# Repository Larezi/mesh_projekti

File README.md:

# BLE mesh projekti
- Yleiskuvaus  
Projektissa toteutetaan BLE mesh -verkko, joka välittää lämpötila- ja ilmankosteusdataa.  
Verkko muodostuu ESP32-moduuleihin perustuvista solmuista,  
joissa käytetään SHTC3-sensoria lämpötilan ja ilmankosteuden mittaamiseen.  
Solmut välittävät mittausdatan pääsolmulle, jonka kautta data siirretään Raspberry Pi:lle.  
Raspberry Pi toimii gatewayna ja tallentaa datan tietokantaan, josta mittaustietoja voidaan lukea web-käyttöliittymän kautta.  

- Lohkokaavio

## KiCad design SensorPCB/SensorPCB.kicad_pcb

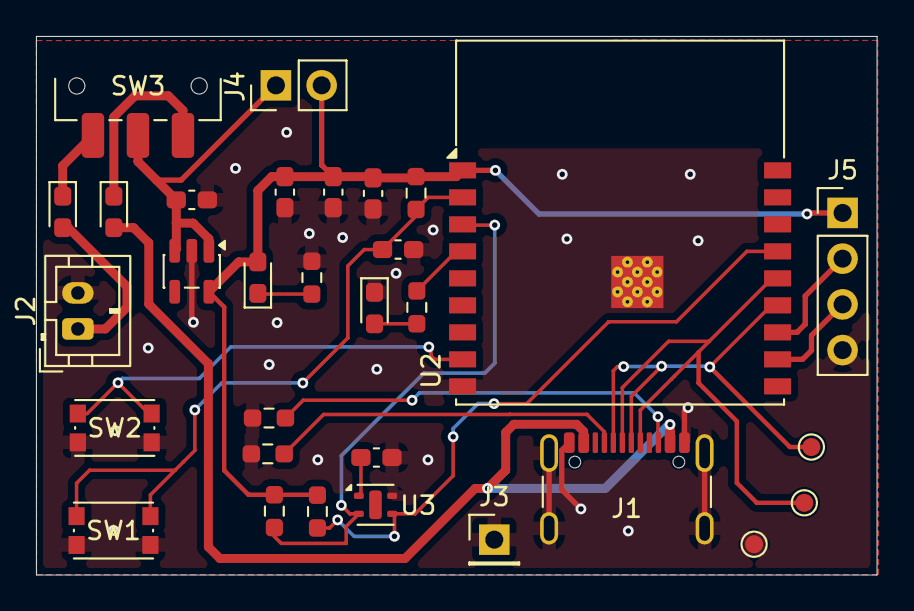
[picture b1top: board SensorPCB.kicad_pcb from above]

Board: 2 copper layers, 46.7 x 29.9 mm, 31 parts (0 on the bottom side), 20 nets.

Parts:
C1, C2: 1uF; C_0603_1608Metric_Pad1.08x0.95mm_HandSolder
C3: 10uF; C_0603_1608Metric_Pad1.08x0.95mm_HandSolder
C4: 0.1uF; C_0603_1608Metric_Pad1.08x0.95mm_HandSolder
C5: C; C_0603_1608Metric_Pad1.08x0.95mm_HandSolder
C6: 100nF; C_0603_1608Metric_Pad1.08x0.95mm_HandSolder
D1, D4: D; D_0603_1608Metric_Pad1.05x0.95mm_HandSolder
D2, D3: LED; LED_0603_1608Metric_Pad1.05x0.95mm_HandSolder
J1: USB_C_Receptacle_USB2.0_14P; USB_C_Receptacle_GCT_USB4105-xx-A_16P_TopMnt_Horizontal
J2: Conn_01x02_Pin; JST_PH_B2B-PH-K_1x02_P2.00mm_Vertical
J3: Conn_01x01; PinHeader_1x01_P2.54mm_Vertical
J4: Vin Vout; PinHeader_1x02_P2.54mm_Vertical
J5: V; PinHeader_1x04_P2.54mm_Vertical
R1: 10K; R_0603_1608Metric_Pad0.98x0.95mm_HandSolder
R2, R3: 4.7K; R_0603_1608Metric_Pad0.98x0.95mm_HandSolder
R4, R5: 5.1K; R_0603_1608Metric_Pad0.98x0.95mm_HandSolder
R6, R7: 1K; R_0603_1608Metric_Pad0.98x0.95mm_HandSolder
SW1: RST; SW_Push_1P1T_NO_CK_KMR2
SW2: Boot; SW_Push_1P1T_NO_CK_KMR2
SW3: SW_SPDT; SW_SPDT_CK_JS102011SAQN
TP1, TP2, TP3: TestPoint; TestPoint_Pad_D1.0mm
U1: AP2112K; SOT-23-5
U2: ESP32-C3-WROOM-02
U3: SHTC3; Sensirion_DFN-4-1EP_2x2mm_P1mm_EP0.7x1.6mm

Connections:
/BATT Power: D4.2 (A), J2.1
/USB Power: D1.2 (A), J1.A4 (VBUS), J1.A9 (VBUS), J1.B4 (VBUS), J1.B9 (VBUS)
GND: C1.2, C2.2, C3.2, C4.2, C5.2, C6.1, D2.1 (K), J1.A1 (GND), J1.A12 (GND), J1.B1 (GND), J1.B12 (GND), J1.SH (SHIELD), J2.2, J3.1 (Pin_1_1), J5.4, R4.1, R5.1, R7.2, SW1.1, SW2.1, TP1.1 (1_1), U1.2 (GND), U2.9 (GND), U2.19 (GND), U3.4 (VSS)
unnamed: D1.1 (K), SW3.1 (A)
unnamed: D2.2 (A), R6.1
unnamed: C2.1, C3.1, C4.1, C6.2, D3.2 (A), J4.2, J5.1, R1.2, R2.1, R3.1, U1.5 (VOUT), U2.1 (3V3), U3.1 (VDD)
unnamed: D3.1 (K), R7.1
unnamed: D4.1 (K), SW3.3 (C)
unnamed: J1.A5 (CC1), R5.2
unnamed: J1.B5 (CC2), R4.2
unnamed: C1.1, J4.1, SW3.2 (B), U1.1 (VIN), U1.3 (EN)
unnamed: J5.2, U2.12 (IO21/TXD)
unnamed: J5.3, U2.11 (IO20/RXD)
unnamed: C5.1, R1.1, SW1.2, U2.2 (EN)
unnamed: R3.2, U2.15 (IO3), U3.3 (SDA)
unnamed: R2.2, U2.3 (IO4), U3.2 (SCL)
unnamed: R6.2, U2.4 (IO5)
unnamed: SW2.2, U2.8 (IO9)
unnamed: J1.A7 (D-), J1.B7 (D-), TP2.1 (1_1), U2.13 (IO18)
unnamed: J1.A6 (D+), J1.B6 (D+), TP3.1 (1_1), U2.14 (IO19)
